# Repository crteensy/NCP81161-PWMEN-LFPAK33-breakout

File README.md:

# NCP81161-PWMEN-LFPAK33-breakout
Breakout board for NCP81161 gate drivers with PWM and EN inputs and FETs in LFPAK33 like the PSMN1R8-30MLH

## First test successful
The board was tested with an

- STM32G071 (breakout board here: https://github.com/crteensy/STM32G071GBU6_breakout)
- running an experimental branch of AM32, PWM/EN target
- DShot input through a Mamba F405 Mini
- Motor: Mamba 1408 4000KV
- PSU set to 5V, 500 mA current limit

This breakout board is designed to facilitate testing of PWM/EN-type firmware on e.g. the STM32G071GBU6 (see here for a matching MCU breakout board: https://github.com/crteensy/STM32G071GBU6_breakout)

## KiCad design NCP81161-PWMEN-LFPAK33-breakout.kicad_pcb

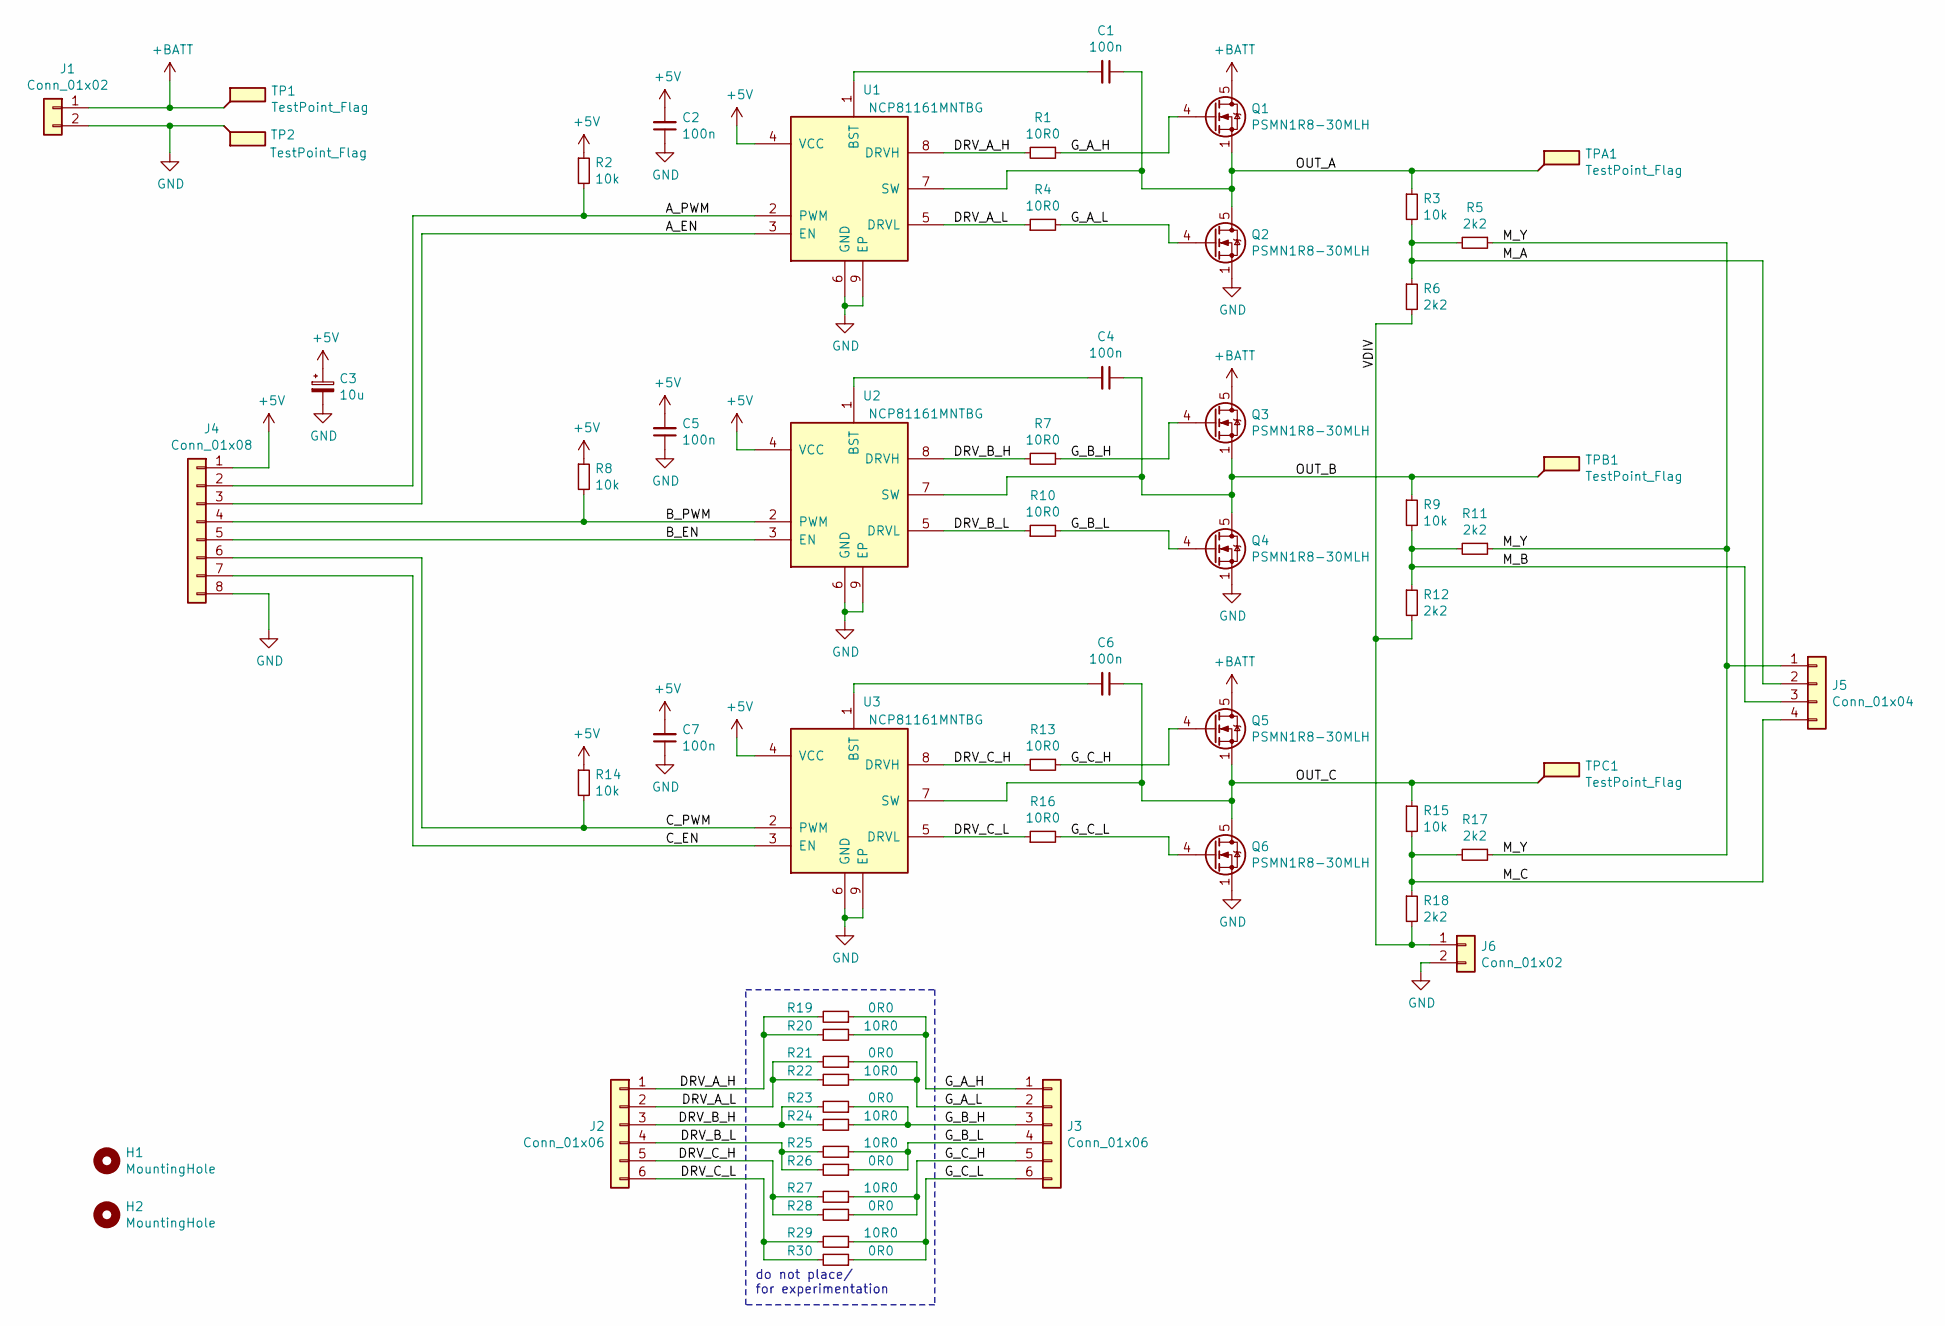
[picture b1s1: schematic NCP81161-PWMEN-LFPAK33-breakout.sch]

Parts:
C1, C2, C4, C5, C6, C7: 100n; C_0603_1608Metric
C3: 10u; CP_EIA-3216-18_Kemet-A
H1, H2: MountingHole; MountingHole_3.5mm
J1, J6: Conn_01x02; PinHeader_1x02_P2.54mm_Vertical
J2, J3: Conn_01x06; PinHeader_1x06_P2.54mm_Vertical
J4: Conn_01x08; PinHeader_1x08_P2.54mm_Vertical
J5: Conn_01x04; PinHeader_1x04_P2.54mm_Vertical
Q1, Q2, Q3, Q4, Q5, Q6: PSMN1R8-30MLH; LFPAK33
R1, R4, R7, R10, R13, R16, R20, R22, R24, R25, R27, R29: 10R0; R_0603_1608Metric
R2, R3, R8, R9, R14, R15: 10k; R_0603_1608Metric
R5, R6, R11, R12, R17, R18: 2k2; R_0603_1608Metric
R19, R21, R23, R26, R28, R30: 0R0; R_0603_1608Metric
TP1, TP2: TestPoint_Flag; TestPoint_Pad_3.0x3.0mm
TPA1: TestPoint_Flag; TestPoint_Pad_2.0x2.0mm
TPB1: TestPoint_Flag; TestPoint_Pad_2.0x2.0mm
TPC1: TestPoint_Flag; TestPoint_Pad_2.0x2.0mm
U1, U2, U3: NCP81161MNTBG; DFN-8-1EP_2x2mm_P0.5mm_EP0.9x1.3mm

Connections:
+5V: C2.2, C3.1, C5.2, C7.2, J4.1, R2.1, R8.1, R14.1, U1.4 (VCC), U2.4 (VCC), U3.4 (VCC)
+BATT: J1.1, Q1.5 (D), Q3.5 (D), Q5.5 (D), TP1.1
/A_EN: J4.3, U1.3 (EN)
/A_PWM: J4.2, R2.2, U1.2 (PWM)
/B_EN: J4.5, U2.3 (EN)
/B_PWM: J4.4, R8.2, U2.2 (PWM)
/C_EN: J4.7, U3.3 (EN)
/C_PWM: J4.6, R14.2, U3.2 (PWM)
/DRV_A_H: J2.1, R1.2, R19.2, R20.1, U1.8 (DRVH)
/DRV_A_L: J2.2, R4.1, R21.2, R22.1, U1.5 (DRVL)
/DRV_B_H: J2.3, R7.2, R23.2, R24.1, U2.8 (DRVH)
/DRV_B_L: J2.4, R10.1, R25.2, R26.2, U2.5 (DRVL)
/DRV_C_H: J2.5, R13.2, R27.2, R28.2, U3.8 (DRVH)
/DRV_C_L: J2.6, R16.1, R29.2, R30.2, U3.5 (DRVL)
/G_A_H: J3.1, Q1.4 (G), R1.1, R19.1, R20.2
/G_A_L: J3.2, Q2.4 (G), R4.2, R21.1, R22.2
/G_B_H: J3.3, Q3.4 (G), R7.1, R23.1, R24.2
/G_B_L: J3.4, Q4.4 (G), R10.2, R25.1, R26.1
/G_C_H: J3.5, Q5.4 (G), R13.1, R27.1, R28.1
/G_C_L: J3.6, Q6.4 (G), R16.2, R29.1, R30.1
/M_A: J5.2, R3.2, R5.2, R6.1
/M_B: J5.3, R9.2, R11.2, R12.1
/M_C: J5.4, R15.2, R17.2, R18.1
/M_Y: J5.1, R5.1, R11.1, R17.1
/OUT_A: C1.1, Q1.1 (S), Q1.2 (S), Q1.3 (S), Q2.5 (D), R3.1, TPA1.1, U1.7 (SW)
/OUT_B: C4.1, Q3.1 (S), Q3.2 (S), Q3.3 (S), Q4.5 (D), R9.1, TPB1.1, U2.7 (SW)
/OUT_C: C6.1, Q5.1 (S), Q5.2 (S), Q5.3 (S), Q6.5 (D), R15.1, TPC1.1, U3.7 (SW)
/VDIV: J6.1, R6.2, R12.2, R18.2
GND: C2.1, C3.2, C5.1, C7.1, J1.2, J4.8, J6.2, Q2.1 (S), Q2.2 (S), Q2.3 (S), Q4.1 (S), Q4.2 (S), Q4.3 (S), Q6.1 (S), Q6.2 (S), Q6.3 (S), TP2.1, U1.6 (GND), U1.9 (EP), U2.6 (GND), U2.9 (EP), U3.6 (GND), U3.9 (EP)
unnamed: C1.2, U1.1 (BST)
unnamed: C4.2, U2.1 (BST)
unnamed: C6.2, U3.1 (BST)

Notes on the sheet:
do not place/ for experimentation

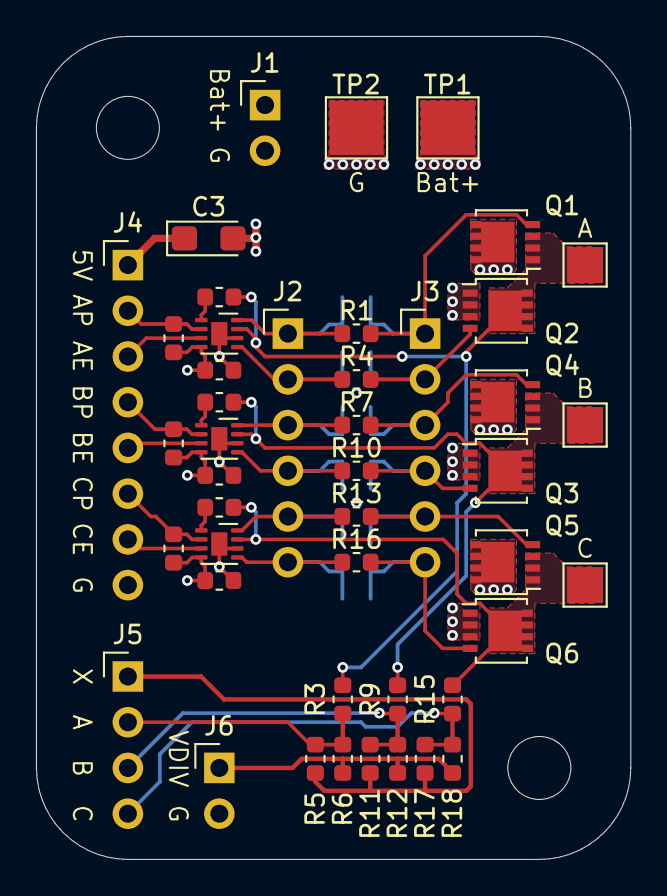
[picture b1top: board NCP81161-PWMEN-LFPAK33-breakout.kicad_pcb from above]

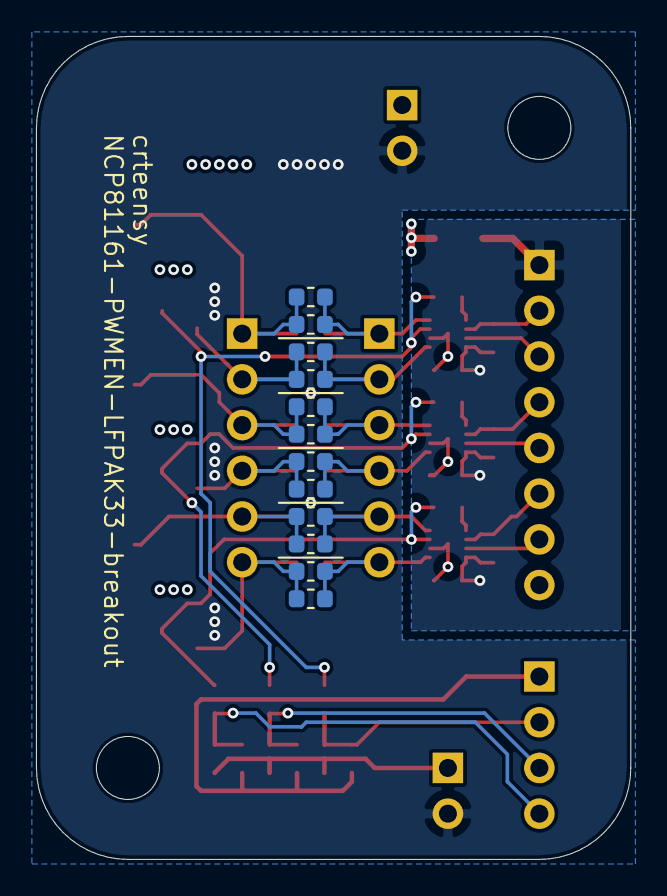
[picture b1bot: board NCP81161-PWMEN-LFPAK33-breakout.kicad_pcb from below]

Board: 4 copper layers, 33.0 x 45.7 mm, 59 parts (12 on the bottom side), 32 nets.

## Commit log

2021-01-29 initial layout files, untested
2021-01-29 Update README.md
    "untested" just to be sure...
